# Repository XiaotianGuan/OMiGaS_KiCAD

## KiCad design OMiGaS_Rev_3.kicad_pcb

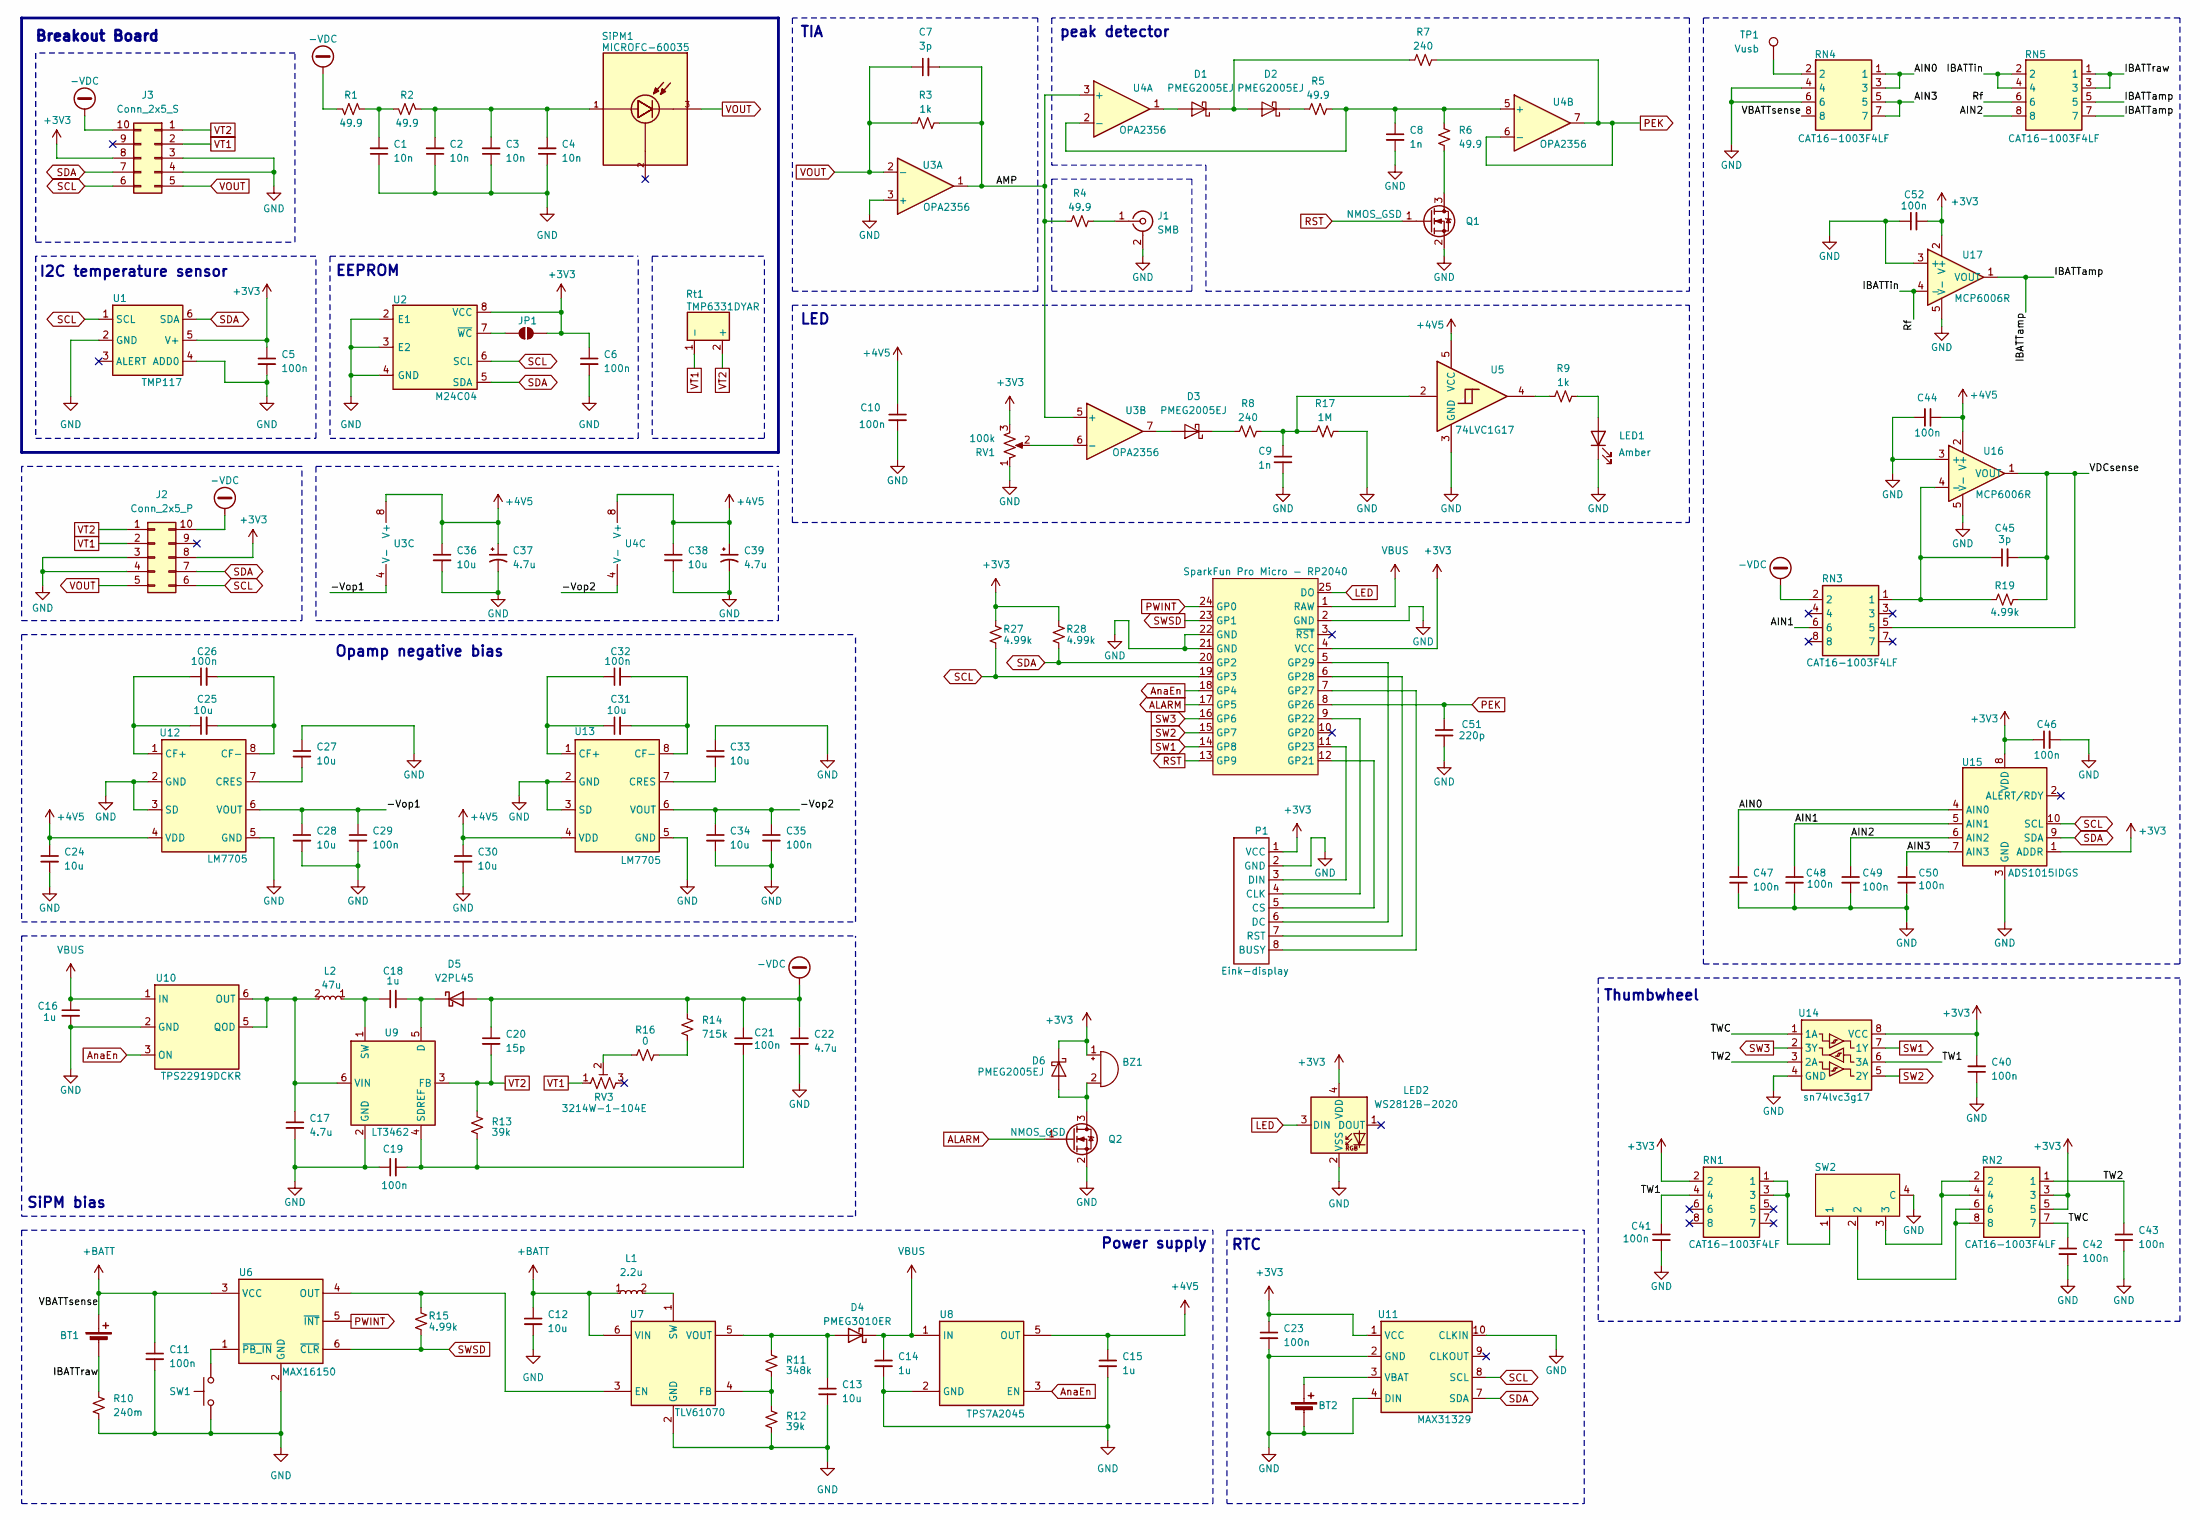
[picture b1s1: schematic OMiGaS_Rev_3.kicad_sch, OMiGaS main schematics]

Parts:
A1: SparkFun Pro Micro - RP2040
BT1: Battery_Cell; TestPoint_2Pads_Pitch2.54mm_Drill0.8mm
BT2: Battery_Cell; BatteryHolder_LINX_BAT-HLD-012-SMT; Manufacturer_Part_Number BAT-HLD-012-SMT
BZ1: Buzzer; Buzzer-0905
C1, C2, C3, C4: 10n; C_0603_1608Metric; Manufacturer_Part_Number C1608C0G2A103J080AC
C5, C6, C10, C11, C19, C21, C23, C26, C29, C32, C35, C40, C41, C42, C43, C44, C46, C47, C48, C49, C50, C52: 100n; C_0603_1608Metric
C7, C45: 3p; C_0603_1608Metric
C8: 1n; C_0603_1608Metric; Manufacturer_Part_Number ECH-U1C102GX5
C9: 1n; C_0603_1608Metric
C12, C13, C24, C25, C27, C28, C30, C31, C33, C34, C36, C38: 10u; C_0805_2012Metric
C14, C15, C16: 1u; C_0603_1608Metric
C17, C22: 4.7u; C_0805_2012Metric
C18: 1u; C_0805_2012Metric
C20: 15p; C_0805_2012Metric
C37, C39: 4.7u; CP_EIA-3216-18_Kemet-A; Manufacturer_Part_Number TPSA475M010R1400
C51: 220p; C_0603_1608Metric
D1, D2, D3, D6: PMEG2005EJ; D_SOD-323F; Manufacturer_Part_Number PMEG2005EJ-QX
D4: PMEG3010ER; Nexperia_CFP3_SOD-123W; Manufacturer_Part_Number PMEG3010ER,115
D5: V2PL45; D_TUMD2; Manufacturer_Part_Number V2PL45HM3/H
J1: SMB; smb-vertical
J2: Conn_2x5_P; LB100-G10P-C0R
J3: Conn_2x5_S; LB100-G10S-C0R
JP1: SolderJumper_2_Open; SolderJumper-2_P1.3mm_Open_RoundedPad1.0x1.5mm
L1: 2.2u; NRS5024T2R2NMGJ; Manufacturer_Part_Number NRS5024T2R2NMGJ
L2: 47u; VLCF5020; Manufacturer_Part_Number VLCF5020T-470MR40
LED1: Amber; LED_0603_1608Metric_Pad1.05x0.95mm_HandSolder; Manufacturer_Part_Number 150060AS75000
LED2: WS2812B-2020; LED_WS2812B-2020_PLCC4_2.0x2.0mm
P1: Eink-display; Eink_display
Q1, Q2: NMOS_GSD; SOT-23; Manufacturer_Part_Number T2N7002AK,LM
R1, R2, R4, R5, R6: 49.9; R_0805_2012Metric
R3, R9: 1k; R_0805_2012Metric
R7, R8: 240; R_0805_2012Metric
R10: 240m; R_1206_3216Metric
R11: 348k; R_0805_2012Metric
R12, R13: 39k; R_0805_2012Metric
R14: 715k; R_0805_2012Metric
R15, R19, R27, R28: 4.99k; R_0805_2012Metric
R16: 0; R_0805_2012Metric
R17: 1M; R_0805_2012Metric
RN1, RN2, RN3, RN4, RN5: CAT16-1003F4LF; CAT16104J4LF; Mouser Part Number 652-CAT16-1003F4LF
RV1: 100k; 35W; Manufacturer_Part_Number TC33X-2-104G
RV3: 3214W-1-104E; 3224W; Manufacturer_Part_Number 3214W-1-104E
Rt1: TMP6331DYAR; Mouser Part Number 595-TMP6331DYAR
SW1: SW_Push; SW_sidemount_1P1T_3x6x3.5
SW2: thumbwheel_3p
SiPM1: MICROFC-60035; PARTREV 31 JUL 2018
TP1: Vusb; TestPoint_Pad_D2.0mm
U1: TMP117; Manufacturer_Part_Number TMP117MAIDRVR
U2: M24C04; M24Cxx; Mouser Part Number 511-M24C16-FMC6TG
U3, U4: OPA2356; SO-8_3.9x4.9mm_P1.27mm; Manufacturer_Part_Number OPA2356AIDR
U5: 74LVC1G17; Manufacturer_Part_Number 74LVC1G17GW,125
U6: MAX16150; SOT95P280X145-6N; Mouser Part Number 700-MAX16150BUT+T
U7: TLV61070; SOT95P280X145-6N; Mouser Part Number 595-TLV61070ADBVR
U8: TPS7A2045; SOT95P280X145-5N; Mouser Part Number 595-TPS7A2045PDBVR
U9: LT3462; Mouser Part Number 584-LT3462ES6#TRMPBF
U10: TPS22919DCKR; Mouser Part Number 595-TPS22919DCKR
U11: MAX31329; Manufacturer_Part_Number MAX31329ELB+
U12, U13: LM7705; VSSOP-8_3.0x3.0mm_P0.65mm; Manufacturer_Part_Number LM7705MMX/NOPB
U14: sn74lvc3g17; SN74LVC3G17; Manufacturer_Part_Number SN74LVC3G17DCTRE4
U15: ADS1015IDGS; TSSOP-10_3x3mm_P0.5mm; Manufacturer_Part_Number ADS1015IDGSR
U16, U17: MCP6006R; Mouser Part Number 579-MCP6006RT-E/OT

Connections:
+3V3: A1.4 (VCC), BZ1.1 (+), C5.1, C6.1, C23.1, C40.2, C46.1, C52.2, D6.1 (K), J2.8, J3.8, JP1.2 (B), LED2.4 (VDD), P1.1 (VCC), R27.1, R28.1, RN1.2, RN2.3, RN2.5, RV1.3, U1.5 (V+), U2.8 (VCC), U11.1 (VCC), U14.8 (VCC), U15.1 (ADDR), U15.8 (VDD), U17.2 (V+)
+4V5: C10.1, C15.1, C24.1, C30.1, C36.1, C37.1, C38.1, C39.1, C44.1, U3.8 (V+), U4.8 (V+), U5.5 (VCC), U8.5 (OUT), U12.4 (VDD), U13.4 (VDD), U16.2 (V+)
+BATT: BT1.1 (+), C11.1, C12.1, L1.1, RN4.8, U6.3 (VCC), U7.6 (VIN)
-VDC: C20.1, C21.1, C22.1, D5.2 (A), J2.10, J3.10, R1.2, R14.1, RN3.2
/-Vop1: C28.1, C29.1, U3.4 (V-), U12.6 (VOUT)
/-Vop2: C34.1, C35.1, U4.4 (V-), U13.6 (VOUT)
/AIN0: C47.1, RN4.1, RN4.3, U15.4 (AIN0)
/AIN1: C48.1, RN3.6, U15.5 (AIN1)
/AIN2: C49.1, RN5.8, U15.6 (AIN2)
/AIN3: C50.1, RN4.5, RN4.7, U15.7 (AIN3)
/AMP: C7.2, R3.2, R4.1, U3.1, U3.5 (+), U4.3 (+)
/IBATTamp: RN5.5, RN5.7, U17.1 (VOUT)
/IBATTin: RN5.2, RN5.4, RN5.6, U17.4 (-)
/IBATTraw: BT1.2 (-), R10.2, RN5.1, RN5.3
/TW1: C41.1, RN1.4, U14.6 (3A)
/TW2: C43.1, RN2.1, U14.3 (2A)
/TWC: C42.1, RN2.7, U14.1 (1A)
/VDCsense: C45.2, R19.2, RN3.5, U16.1 (VOUT)
ALARM: A1.17 (GP5), Q2.1 (G)
AnaEn: A1.18 (GP4), U8.3 (EN), U10.3 (ON)
GND: A1.2 (GND), A1.21 (GND), A1.22 (GND), BT2.2 (-), C1.1, C2.1, C3.1, C4.1, C5.2, C6.2, C8.2, C9.2, C10.2, C11.2, C12.2, C13.2, C14.2, C15.2, C16.2, C17.2, C19.1, C22.2, C23.2, C24.2, C27.1, C28.2, C29.2, C30.2, C33.1, C34.2, C35.2, C36.2, C37.2, C38.2, C39.2, C40.1, C41.2, C42.2, C43.2, C44.2, C46.2, C47.2, C48.2, C49.2, C50.2, C51.2, C52.1, J1.2 (Ext), J2.3, J2.4, J3.3, J3.4, LED1.1 (K), LED2.2 (VSS), P1.2 (GND), Q1.2 (S), Q2.2 (S), R10.1, R12.1, R17.2, RN4.4, RN4.6, RV1.1, SW1.2, SW2.4 (C), U1.2 (GND), U1.4 (ADD0), U2.2 (E1), U2.3 (E2), U2.4 (GND), U3.3 (+), U5.3 (GND), U6.2 (GND), U7.2 (GND), U8.2 (GND), U9.2 (GND), U10.2 (GND), U11.2 (GND), U11.4 (DIN), U11.10 (CLKIN), U12.2 (GND), U12.3 (SD), U12.5 (GND), U13.2 (GND), U13.3 (SD), U13.5 (GND), U14.4 (GND), U15.3 (GND), U16.3 (+), U16.5 (V-), U17.3 (+), U17.5 (V-)
LED: A1.25 (DO), LED2.3 (DIN)
unnamed: A1.12 (GP21), P1.5 (CS)
unnamed: A1.9 (GP22), P1.4 (CLK)
unnamed: A1.11 (GP23), P1.3 (DIN)
unnamed: A1.7 (GP27), P1.8 (BUSY)
unnamed: A1.6 (GP28), P1.7 (RST)
unnamed: A1.5 (GP29), P1.6 (DC)
unnamed: BT2.1 (+), U11.3 (VBAT)
unnamed: BZ1.2 (-), D6.2 (A), Q2.3 (D)
unnamed: C1.2, R1.1, R2.2
unnamed: C2.2, C3.2, C4.2, R2.1, SiPM1.1
unnamed: C9.1, R8.1, R17.1, U5.2
unnamed: D1.2 (A), U4.1
unnamed: D1.1 (K), D2.2 (A), R7.1
unnamed: D2.1 (K), R5.1
unnamed: D3.2 (A), U3.7
unnamed: D3.1 (K), R8.2
unnamed: C13.1, D4.2 (A), R11.2, U7.5 (VOUT)
unnamed: C18.2, D5.1 (K), U9.5 (D)
unnamed: J1.1 (In), R4.2
unnamed: JP1.1 (A), U2.7 (~WC)
unnamed: LED1.2 (A), R9.1
unnamed: Q1.3 (D), R6.2
unnamed: R9.2, U5.4
unnamed: R14.2, R16.2
unnamed: R16.1, RV3.2
unnamed: RN1.1, RN1.3, SW2.1
unnamed: RN2.2, RN2.4, SW2.3
unnamed: RN2.6, RN2.8, SW2.2
unnamed: RN4.2, TP1.1
unnamed: RV1.2, U3.6 (-)
unnamed: C8.1, R5.2, R6.1, U4.2 (-), U4.5 (+)
unnamed: R15.1, U6.4 (OUT), U7.3 (EN)
unnamed: SW1.3, U6.1 (~PB_IN)
unnamed: R11.1, R12.2, U7.4 (FB)
unnamed: L1.2, U7.1 (SW)
unnamed: C19.2, C21.2, R13.2, U9.4 (SDREF)
unnamed: C18.1, L2.1, U9.1 (SW)
unnamed: C17.1, L2.2, U9.6 (VIN), U10.5 (QOD), U10.6 (OUT)
unnamed: C25.1, C26.1, U12.1 (CF+)
unnamed: C25.2, C26.2, U12.8 (CF-)
unnamed: C27.2, U12.7 (CRES)
unnamed: C31.1, C32.1, U13.1 (CF+)
unnamed: C31.2, C32.2, U13.8 (CF-)
unnamed: C33.2, U13.7 (CRES)
unnamed: C45.1, R19.1, RN3.1, U16.4 (-)
PEK: A1.8 (GP26), C51.1, R7.2, U4.6 (-), U4.7
PWINT: A1.24 (GP0), U6.5 (~INT)
RST: A1.13 (GP9), Q1.1 (G)
SCL: A1.19 (GP3), J2.6, J3.6, R27.2, U1.1 (SCL), U2.6 (SCL), U11.8 (SCL), U15.10 (SCL)
SDA: A1.20 (GP2), J2.7, J3.7, R28.2, U1.6 (SDA), U2.5 (SDA), U11.7 (SDA), U15.9 (SDA)
SW1: A1.14 (GP8), U14.7 (1Y)
SW2: A1.15 (GP7), U14.5 (2Y)
SW3: A1.16 (GP6), U14.2 (3Y)
SWSD: A1.23 (GP1), R15.2, U6.6 (~CLR)
VBUS: A1.1 (RAW), C14.1, C16.1, D4.1 (K), U8.1 (IN), U10.1 (IN)
VOUT: C7.1, J2.5, J3.5, R3.1, SiPM1.3, U3.2 (-)
VT1: J2.2, J3.2, RV3.1, Rt1.1 (-)
VT2: C20.2, J2.1, J3.1, R13.1, Rt1.2 (+), U9.3 (FB)

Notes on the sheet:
Power supply
RTC
peak detector
Breakout Board
Thumbwheel
I2C temperature sensor
Opamp negative bias
TIA
EEPROM
LED
SiPM bias

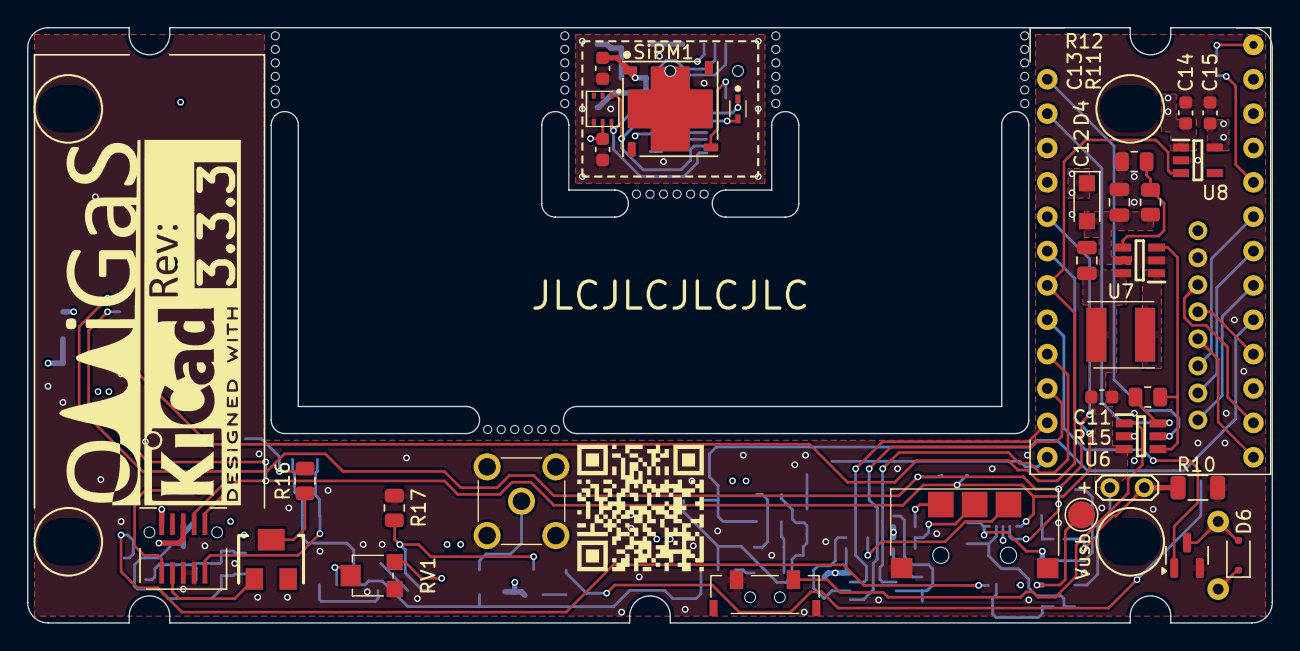
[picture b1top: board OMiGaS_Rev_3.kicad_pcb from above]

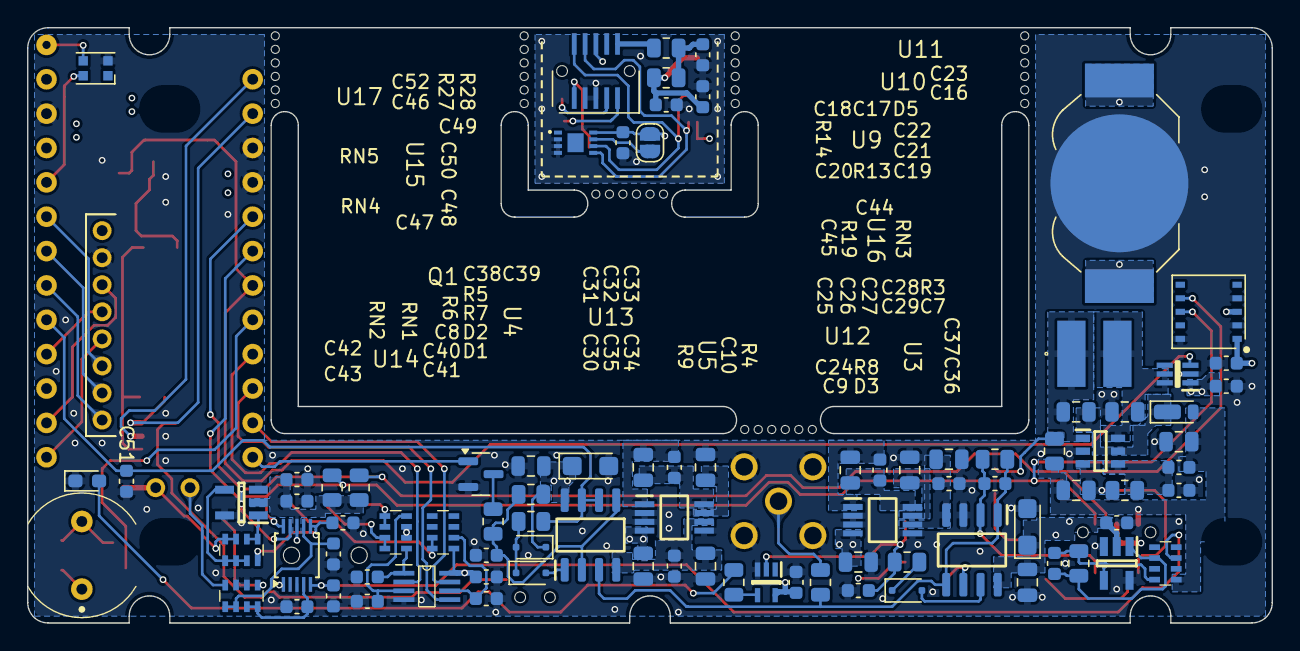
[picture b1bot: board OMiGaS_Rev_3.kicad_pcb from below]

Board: 4 copper layers, 92.0 x 44.0 mm, 122 parts (90 on the bottom side), 80 nets.

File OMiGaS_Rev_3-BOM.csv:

"Reference","Value","Footprint","Qty","Manufacturer_Part_Number","Comments"
"A1","SparkFun Pro Micro - RP2040","OMiGaS:SparkFun Pro Micro - RP2040","1","",""
"BT1","Battery_Cell","TestPoint:TestPoint_2Pads_Pitch2.54mm_Drill0.8mm","1","",""
"BT2","Battery_Cell","Battery:BatteryHolder_LINX_BAT-HLD-012-SMT","1"," BAT-HLD-012-SMT",""
"BZ1","Buzzer","OMiGaS:Buzzer-0905","1","",""
"C1,C2,C3,C4","10n","Capacitor_SMD:C_0603_1608Metric","4","C1608C0G2A103J080AC","C0G dielectic"
"C5,C6,C10,C11,C19,C21,C23,C26,C29,C32,C35,C40,C41,C42,C43,C44,C46,C47,C48,C49,C50,C52","100n","Capacitor_SMD:C_0603_1608Metric","22","",""
"C7,C45","3p","Capacitor_SMD:C_0603_1608Metric","2","",""
"C8","1n","Capacitor_SMD:C_0603_1608Metric","1"," ECH-U1C102GX5","Preferably film caps"
"C9","1n","Capacitor_SMD:C_0603_1608Metric","1","",""
"C12,C13,C24,C25,C27,C28,C30,C31,C33,C34,C36,C38","10u","Capacitor_SMD:C_0805_2012Metric","12","",""
"C14,C15,C16","1u","Capacitor_SMD:C_0603_1608Metric","3","",""
"C17,C22","4.7u","Capacitor_SMD:C_0805_2012Metric","2","",""
"C18","1u","Capacitor_SMD:C_0805_2012Metric","1","",""
"C20","15p","Capacitor_SMD:C_0805_2012Metric","1","",""
"C37,C39","4.7u","Capacitor_Tantalum_SMD:CP_EIA-3216-18_Kemet-A","2"," TPSA475M010R1400",""
"C51","220p","Capacitor_SMD:C_0603_1608Metric","1","",""
"D1,D2,D3,D6","PMEG2005EJ","Diode_SMD:D_SOD-323F","4","PMEG2005EJ-QX",""
"D4","PMEG3010ER","Diode_SMD:Nexperia_CFP3_SOD-123W","1","PMEG3010ER,115",""
"D5","V2PL45","Diode_SMD:D_TUMD2","1"," V2PL45HM3/H",""
"J1","SMB","OMiGaS:smb-vertical","1","",""
"J2","Conn_2x5_P","OMiGaS:LB100-G10P-C0R","1","","Molex 524651070 compatible"
"J3","Conn_2x5_S","OMiGaS:LB100-G10S-C0R","1","","Warning: This socket is NOT compatible with Molex 533091070, the snap height (actually weidth) is different"
"L1","2.2u","OMiGaS:NRS5024T2R2NMGJ","1","NRS5024T2R2NMGJ",""
"L2","47u","OMiGaS:VLCF5020","1","VLCF5020T-470MR40",""
"LED1","Amber","LED_SMD:LED_0603_1608Metric_Pad1.05x0.95mm_HandSolder","1","150060AS75000",""
"LED2","WS2812B-2020","LED_SMD:LED_WS2812B-2020_PLCC4_2.0x2.0mm","1","",""
"P1","Eink-display","OMiGaS:Eink_display","1","",""
"Q1,Q2","NMOS_GSD","Package_TO_SOT_SMD:SOT-23","2"," T2N7002AK,LM",""
"R1,R2,R4,R5,R6","49.9","Resistor_SMD:R_0805_2012Metric","5","",""
"R3,R9","1k","Resistor_SMD:R_0805_2012Metric","2","",""
"R7,R8","240","Resistor_SMD:R_0805_2012Metric","2","",""
"R10","240m","Resistor_SMD:R_1206_3216Metric","1","",""
"R11","348k","Resistor_SMD:R_0805_2012Metric","1","",""
"R12,R13","39k","Resistor_SMD:R_0805_2012Metric","2","",""
"R14","715k","Resistor_SMD:R_0805_2012Metric","1","",""
"R15,R19,R27,R28","4.99k","Resistor_SMD:R_0805_2012Metric","4","",""
"R16","0","Resistor_SMD:R_0805_2012Metric","1","",""
"R17","1M","Resistor_SMD:R_0805_2012Metric","1","",""
"RN1,RN2,RN3,RN4,RN5","CAT16-1003F4LF","OMiGaS:CAT16104J4LF","5","CAT16-1003F4LF",""
"Rt1","TMP6331DYAR","OMiGaS:TMP6331DYAR","1","TMP6331DYAR",""
"RV1","100k","OMiGaS:35W","1"," TC33X-2-104G",""
"RV3","3214W-1-104E","OMiGaS:3224W","1","3214W-1-104E",""
"SiPM1","MICROFC-60035","OMiGaS:MICROFC-60035","1","MICROFC-60035-SMT-TR",""
"SW1","SW_Push","OMiGaS:SW_sidemount_1P1T_3x6x3.5","1","",""
"SW2","~","OMiGaS:thumbwheel_3p","1","",""
"TP1","Vusb","TestPoint:TestPoint_Pad_D2.0mm","1","",""
"U1","TMP117","OMiGaS:TMP117","1","TMP117MAIDRVR",""
"U2","M24C04","OMiGaS:M24Cxx","1","M24C04-RMC6TG",""
"U3,U4","OPA2356","Package_SO:SO-8_3.9x4.9mm_P1.27mm","2","OPA2356AIDR",""
"U5","74LVC1G17","OMiGaS:74LVC1G17","1","74LVC1G17GW,125",""
"U6","MAX16150","OMiGaS:SOT95P280X145-6N","1"," MAX16150AUT+T",""
"U7","TLV61070","OMiGaS:SOT95P280X145-6N","1","TLV61070ADBVR",""
"U8","TPS7A2045","OMiGaS:SOT95P280X145-5N","1"," TPS7A2045PDBVR",""
"U9","LT3462","OMiGaS:LT3462","1"," LT3462ES6#TRMPBF",""
"U10","TPS22919DCKR","OMiGaS:TPS22919DCKR","1"," TPS22919DCKR",""
"U11","MAX31329","OMiGaS:MAX31329","1","MAX31329ELB+",""
"U12,U13","LM7705","Package_SO:VSSOP-8_3.0x3.0mm_P0.65mm","2","LM7705MMX/NOPB",""
"U14","sn74lvc3g17","OMiGaS:SN74LVC3G17","1","SN74LVC3G17DCTRE4",""
"U15","ADS1015IDGS","Package_SO:TSSOP-10_3x3mm_P0.5mm","1","ADS1015IDGSR",""
"U16,U17","MCP6006R","OMiGaS:MCP6006R","2","MCP6006RT-E/OT",""

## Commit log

2024-07-17 v3.3.1 initial commit
2024-07-17 added test file
2024-07-17 deleted temp file
2024-09-12 edited .gitignore, untracked unnecessary files
2024-09-12 deleted cached untracked files
2024-10-01 Added BOM, optimized trim pot position, re-generated gerber
2024-10-02 Updated BOM, added 3d model for B2B connector, corrected detector shell position
2024-10-03 updated BOM
2024-10-03 fixed typo in BOM
2024-10-04 edited schematics signature
2024-12-22 changed to through hole pogo pin, improved ground stitching

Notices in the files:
parts and their libraries:
Copyright 2021 Accelerated Designs. All rights reserved.
